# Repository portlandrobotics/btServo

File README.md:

btServo
=======

PARTS hobby servo controller project

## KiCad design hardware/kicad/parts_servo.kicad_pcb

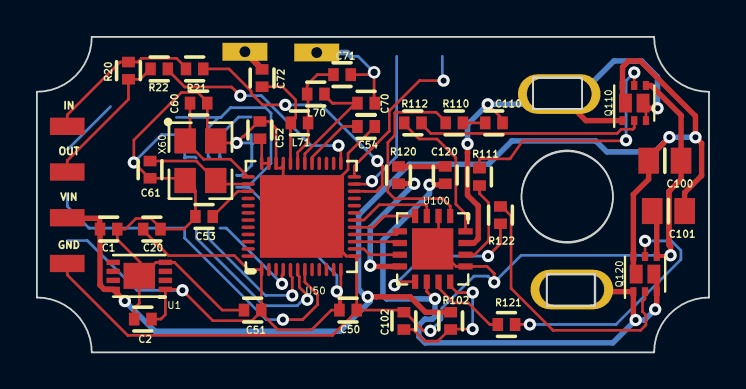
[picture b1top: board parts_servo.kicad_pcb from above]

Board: 2 copper layers, 37.3 x 17.5 mm, 47 parts (0 on the bottom side), 43 nets.

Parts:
C1: 1uF 10V; 0402-B
C2, C102, C110, C120: 1uF; 0402-B
C20, C50, C51, C53, C203: 0.1uF; 0402-B
C52: 0.001uF; 0402-B
C54: 0.047uF; 0402-B
C60, C61: 8pF; 0402-B
C70: 0.0022uF; 0402-B
C71: np; 0402-B
C72: 2,2pF; 0402-B
C100, C101: 10uF 10V; 0805-B
C204: 4u7; 0402-B
JP1, JP3: M01; SMDMOTOR
JP2: Input; SMD_1X4_HEADER
JP4: SWD; SMD_1X3_PADS
JP5: POT; SMD_1X3_PADS
L70: 10nH; 0402-B
L71: 4.7nH; 0402-B
Q110, Q120: NFET-DUAL; PMDPB28UN
R20: 120 (np); 0402-B
R21, R22: 4.7K (np); 0402-B
R102, R111, R112, R121, R122: 2.2; 0402-B
R110, R120: 1; 0402-B
R201: 15; 0402-B
TP1: ANT1; TESTPOINT-(1X1)CREAMED
TP2: ANT_FEED; TESTPOINT-(1X1)CREAMED
U1: MCP1703-3302; MCP1703
U50: NRF51822
U100: RT9625A; QFN-16(4X4)+EP
U200: AS5050
X60: 16MHz; CRYSTAL-3.2X2.5(4_TERMINAL)

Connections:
+3.3V: C2.1, C20.1, C50.1, C51.1, C203.1, JP5.3, R201.2, U1.1, U50.1, U50.12, U200.11, U200.14
/PWR_IN: C1.1, C100.1, C101.1, JP2.2, Q110.6, Q110.P7, Q120.6, Q120.P7, R102.2, U1.8
/PWR_MotorA: C120.2, JP1.1, Q120.1, Q120.3, Q120.P8, U100.10
/PWR_MotorB: C110.2, JP3.1, Q110.1, Q110.3, Q110.P8, U100.15
/UNIPOLAR_INPUT: R21.2, U50.22
/UNIPOLAR_OUTPUT: R22.2, U50.25
AVDD: C52.1, U50.35, U50.36
GND: C1.2, C2.2, C20.2, C50.2, C51.2, C52.2, C53.2, C54.2, C60.2, C61.2, C70.2, C71.2, C100.2, C101.2, C102.2, C203.2, C204.1, JP2.1, JP4.3, JP5.1, Q110.4, Q120.4, TP1.TP, U1.4, U1.PAD, U50.13, U50.33, U50.34, U50.PAD, U100.2, U100.13, U100.PAD, U200.9, U200.10, U200.13, X60.2, X60.4
unnamed: C53.1, U50.39
unnamed: C54.1, U50.29
unnamed: C60.1, U50.37, X60.1
unnamed: C61.1, U50.38, X60.3
unnamed: C70.1, L70.2, U50.30
unnamed: C71.1, L70.1, L71.2, U50.31
unnamed: C72.1, L71.1, U50.32
unnamed: C72.2, TP2.TP
unnamed: C102.1, R102.1, U100.12
unnamed: C110.1, R110.2
unnamed: C120.1, R120.2
unnamed: C204.2, R201.1, U200.12
unnamed: JP2.3, R20.2, R22.1
unnamed: JP2.4, R20.1, R21.1
unnamed: JP4.1, U50.24
unnamed: JP4.2, U50.23
unnamed: JP5.2, U50.7, U200.4
unnamed: Q110.2, R112.2
unnamed: Q110.5, R111.2
unnamed: Q120.2, R122.2
unnamed: Q120.5, R121.2
unnamed: R110.1, U100.1
unnamed: R111.1, U100.14
unnamed: R112.1, U100.16
unnamed: R120.1, U100.8
unnamed: R121.1, U100.11
unnamed: R122.1, U100.9
unnamed: U50.18, U100.3
unnamed: U50.17, U100.4
unnamed: U50.16, U100.5
unnamed: U50.15, U100.6
unnamed: U50.14, U100.7
unnamed: U50.4, U200.1
unnamed: U50.5, U200.2
unnamed: U50.6, U200.3

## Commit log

2014-04-14 Initial prototype design by Tim
2014-04-15 Add pinswaps to nRF
2014-04-15 Initial layout
2014-04-15 Removed all the DRC errors.
2014-04-15 resize vias for LPKF
2014-04-15 Fix DRC errors from via resize
2014-04-15 Fatten some traces, fix DRC and routing
2014-04-15 Move programming header to edge of board
2014-04-16 Connect the center pad on the QFN48 to GND.
2014-04-16 Connect NRF center pad to GND. Add ground pour on bottom of board to improve current return from motor FETs.
2014-04-16 Clean up silkscreen text
2014-04-16 Set bottom fill to net GND. Added mounting holes and a few extra GND vias.
2014-05-07 Initial firmware test based on Nordic pwm code
2014-05-13 Added ADC read code, and a basic PWM function. Replaced main loop to call them.
2014-06-10 First pass at BLE radio control of servo. Very crude proportional control based on potentiometer feedback. Radio code based on Nordic BLE based UART example.
2014-07-24 Disable timeout by switching to general discovery mode. Implement new communication protocol and register map.
2014-07-24 Make register address 16 bits.
2014-09-08 Second rev of board design. Shrink to servo case size
2014-09-10 Update pin mapping for new board and SPI commands for the AS5050. Doesn't seem to work though.
2014-09-12 Wrote some AS5050 code to reset the chip on boot and if it reports an error. This is all untested, since I don't have a working part at the moment.
2014-09-12 Fix factor of 4 error in position reading.
2014-09-12 fix bitmask typo
2015-01-05 Add first version of KiCAD hardware files
2015-01-14 Fix incorrect connections on AS5050
2015-03-17 New board layout. Version sent to DirtyPCBs for thinner boards
2015-04-11 Initial commit of prototype android app.
2015-04-21 Rev protocol to add command to response message. Add target arrow to wheel display. Add motor switch.
2015-04-21 Rev protocol to add command to response. Add OFF mode.
2015-05-14 correct motor direction control (reverse it)
2015-05-14 board layout cleanup
2015-08-31 Add pi filter to matching network. Clean up routing and create parts_servo2.kicad_pcb with latest changes
2015-09-15 new board layout: parts_servo3.kicad_pcb
2016-06-07 Update PCB
2016-06-07 Update firmware to use nRF51 V9 SDK with standard GCC Makefile and Eclipse project
